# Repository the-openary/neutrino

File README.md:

# Neutrino

### Overview

This is Neutrino! It's a portable 3D printer that is meant to be cheap and accessible - it fits inside a filament box! ~~Currently in development~~ currently unfinished, do NOT try building your own without messaging me for help for now. Join the the Discord server [here!](https://discord.gg/VZFWGp7FHZ). Made by @qcoral

The `dev_process` folder contains a selection of notes & data that provide a peek into the development process of this printer. Due to privacy reasons it is only a snippet. If there's something specific feel free to reach out. 

### Features
- Fits in a 200x200x70mm volume
- Under $300 CAD (using the attached BOM)
- Uses common, off-the-shelf parts
- Mostly self replicating

*currently the base cannot be self-printed

## 2025-12-12 Update:

I last updated this printer almost 2 years ago in 2024. The printer works, but the useability could definitely be improved.

While I would love to someday really put in the polish to properly finish this design, I really am not sure when that would be. Many of the parts would have to be redesigned from scratch, and I've recently been enjoying other projects much more. That being said, this was still an absolute blast to work on!

Feel free to fork this if you so desire. All I ask is that you give proper attribution!

---
### Getting started

In the root of the repository is a file called `BOM.xlsx`. Contains all the relevant links, notes, etc. Currently missing screw counts, please use the CAD for that!

Join the discord for help, I will gladly give guidance on how to build your own.

---
### FAQ:

**Can I see a video?**

There are short clips that can be found in the discord. Currently working on a proper release video, will try and get that out soon<sup>tm</sup>.

**Where's the extruder?**

Great question! Neutrino is designed to use a Sherpa Mini in bowden configuration. Due to copyright, it cannot be included in the CAD. It can be found [here](https://github.com/Annex-Engineering/Sherpa_Mini-Extruder). Totally awesome design.

**Why a Bowden Setup?**

Initially the printer had a Direct Drive setup, but this was later swapped to Bowden. There were a couple reasons for this
- Faster printing
- Short tube length
- Easier maintenance
- Easier to explain to others
    - Being a portable printer, many people who have never seen a 3D printer see it. I think this makes Neutrino double as an educational/inspirational tool and for that reason it is easier to explain the separate parts of a Bowden extruder vs a DD setup. 

**Where can I source my parts?**

Anywhere you can find them. The `BOM.xlsx` file contains links to all the sources that I used during development. The printer itself uses all standard 8mm + M3 hardware. Use AliExpress, Amazon, spare parts, etc. Unfortunately you will need to print your own parts for now, but that will change soon.

**Is there an assembly guide?**

Not yet, working on that soon. For now you should just use the CAD. There is also the [discord](https://discord.gg/VZFWGp7FHZ) for help. I can assist you personally there.

**What is under `OLED_Module`?**

Under OLED_Module is a custom, optional PCB that contains an OLED display, rotary encoder, kill switch, and speaker. The case is still WIP, but the PCB itself has been tested and works well.

**Why the name "Neutrino"?**

The [Positron](https://github.com/KRALYN/PositronV3) project was a huge inspiration for me whilst designing this project. Seeing the innovation process and Kralyn's willingness to tackle problems was a huge motivator for me. While Neutrino was originally a codename, I believe it fits pretty well. 

---

### TODO:

- [ ] Make the base self replicating
- [ ] Misc clearance fixes
- [ ] Add pin breakout connector
- [ ] Add PET Recycling integration

#### [Credits](/CREDITS.md)

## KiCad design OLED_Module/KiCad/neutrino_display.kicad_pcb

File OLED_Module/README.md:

Custom OLED Module for the Neutrino

Pinout for SKR Mini E3 V2.0

```
 *            SKR Mini E3 V2.0
 *                 ------
 * (NONE)    PB5  | 1  2 | PA15 (BTN_ENC)
 * (BTN_EN1) PA9  | 3  4 | RESET
 * (BTN_EN2) PA10   5  6 | PB9  (SDA)
 * (SCL)     PB8  | 7  8 | PB15 (BEEPER)
 *            GND | 9 10 | 5V
 *                 ------
 *                  EXP1
 ```
Source: https://upload.wikimedia.org/wikipedia/commons/9/90/Stm32f103_pinout_diagram.png

Editing Marlin: 
- Add the following to `pins_BTT_SKR_MINI_E3_common.h` under  `#elif HAS_WIRED_LCD`
```C
  #elif ENABLED(OLED_PANEL_TINYBOY2)

    #define BEEPER_PIN EXP1_08_PIN //PB15

    #define BTN_ENC EXP1_02_PIN //PA15
    #define BTN_EN1 EXP1_03_PIN //PA9
    #define BTN_EN2 EXP1_05_PIN //PA10
```
- Then select 
```C 
#define OLED_PANEL_TINYBOY2
``` 
Under the `OLED Displays` section of `configuration.h` (roughly line 2980)

Special thanks to czupryna011 for the instructable I based this off of https://www.instructables.com/Small-and-Cheap-Tiny-OLED-for-Ender-3-stock-and-SK/

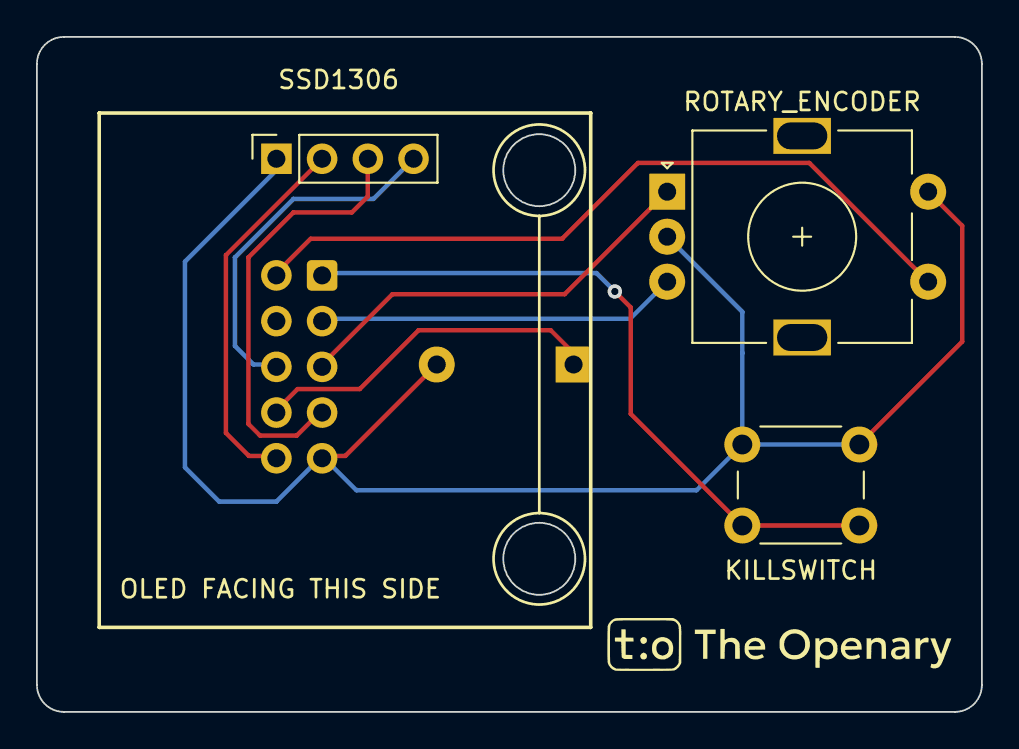
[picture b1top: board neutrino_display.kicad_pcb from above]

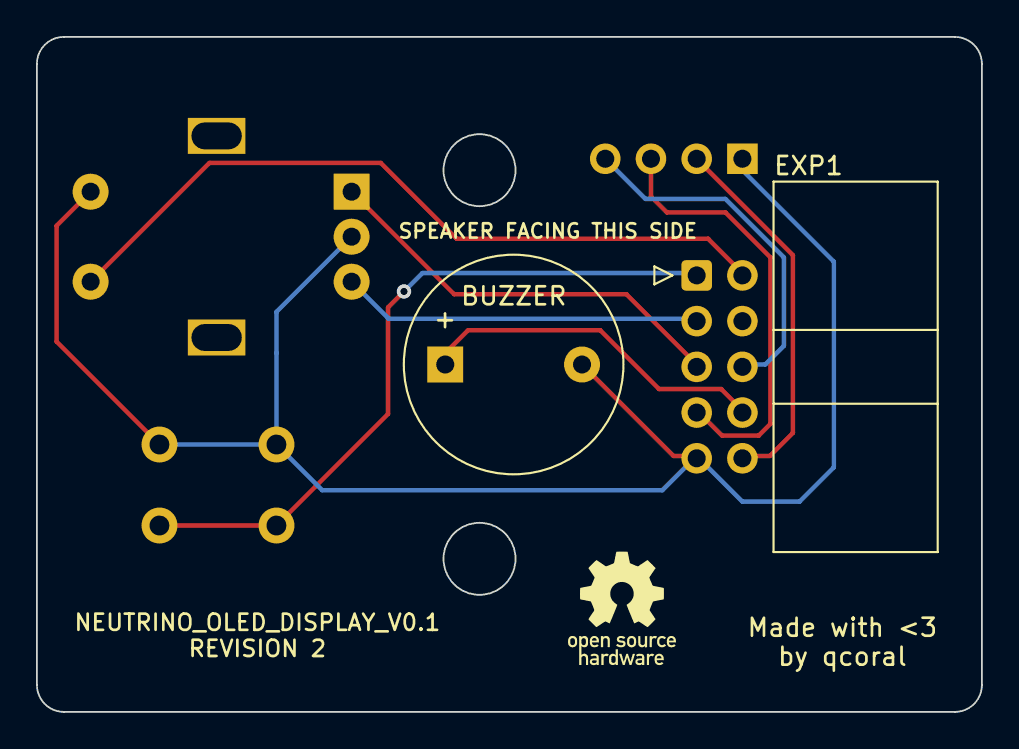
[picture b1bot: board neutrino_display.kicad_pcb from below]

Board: 2 copper layers, 52.5 x 37.5 mm, 5 parts (2 on the bottom side), 9 nets.

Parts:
BUZZER: Buzzer; Buzzer_12x9.5RM7.6
EXP1: 2x5; IDC-Header_2x05_P2.54mm_Horizontal
J2: OLED_Headers; PinSocket_1x04_P2.54mm_Vertical
KILLSWITCH: Kill Switch; SW_PUSH_6mm_H8.5mm
ROTARY_ENCODER: EC11_Switch; RotaryEncoder_Alps_EC11E-Switch_Vertical_H20mm

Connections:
+5V: EXP1.10, J2.2
BTN_EN1: EXP1.3, ROTARY_ENCODER.B
BTN_EN2: EXP1.5, ROTARY_ENCODER.A
BTN_ENC: EXP1.2, ROTARY_ENCODER.S1
GND: BUZZER.2 (+), EXP1.9, J2.1, KILLSWITCH.2, ROTARY_ENCODER.C, ROTARY_ENCODER.S2
KILLSWITCH: EXP1.1, KILLSWITCH.1
SCL: EXP1.7, J2.3
SDA: EXP1.6, J2.4
SPEAKER: BUZZER.1 (-), EXP1.8

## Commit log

2023-12-11 added license
2023-12-12 updated BOM, README.md
2023-12-23 Fixed PCBs, updated firmware, added PrusaSlicer settings, updated README.md, updated BOM. Awesome :)
2026-01-24 updated readme to use local image instead of broken cdn
2026-01-24 Change Neutrino image from JPG to PNG
    Updated image format for Neutrino picture in README.
2026-01-29 moved update message
